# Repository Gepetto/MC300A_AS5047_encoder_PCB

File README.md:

# MC300_AS5047_encoder_PCB
This is a PCB support for a AS5047 magnetic encoder to replace MC300A control board on myactuator RMD-X actuators.

https://ams.com/en/as5047p
https://www.myactuator.com/_files/ugd/cab28a_d12405ad9d114c308658ca2bf5e42c5b.pdf

# Authors 
* Amine El Hamdaoui
* Jerome Manhes
* Thomas Flayols

LAAS CNRS

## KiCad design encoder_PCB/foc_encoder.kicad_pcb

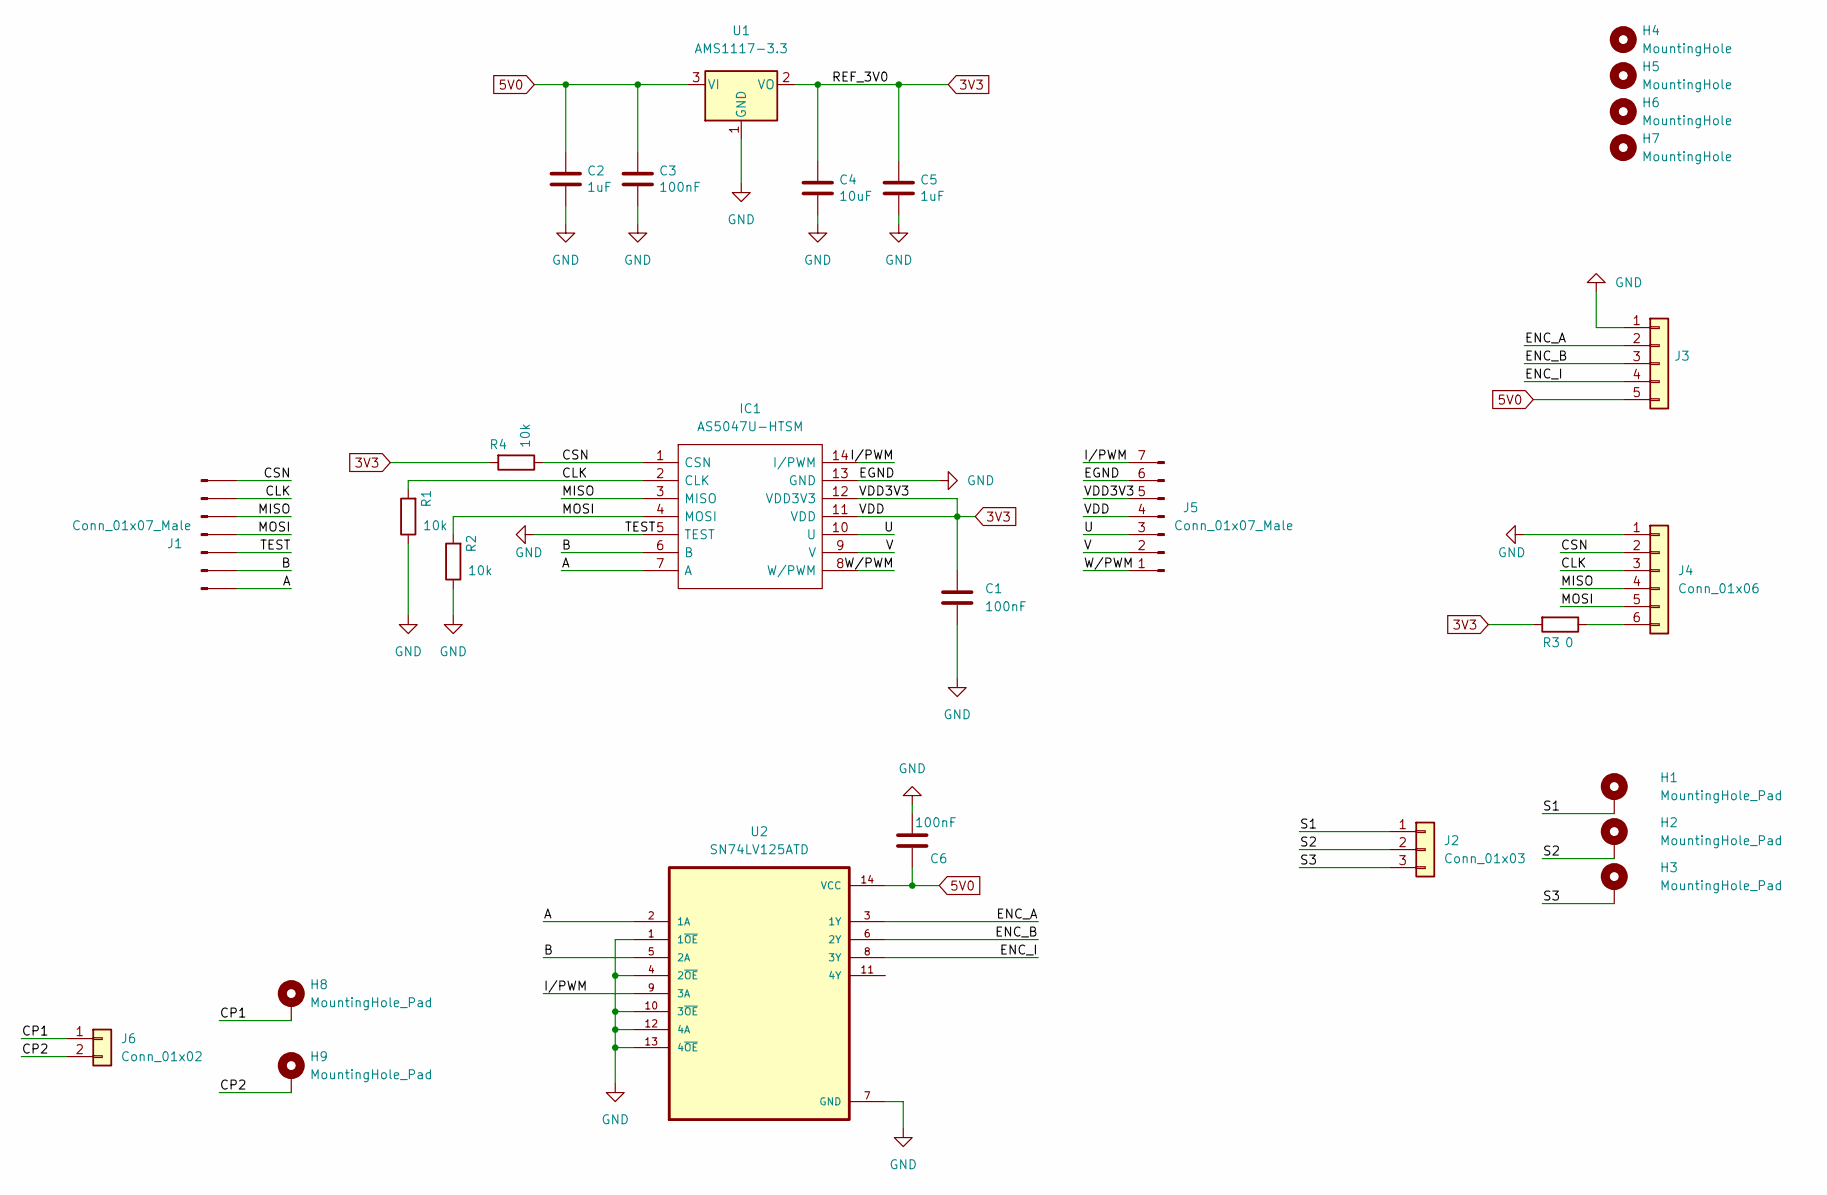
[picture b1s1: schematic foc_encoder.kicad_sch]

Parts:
C1, C6: 100nF; C_0402_1005Metric
C2, C5: 1uF; C_0402_1005Metric; Rated Voltage 10V; Part No GRM033C81A105ME05D; DigiKey 490-13219-1-ND
C3: 100nF; C_0402_1005Metric; Rated Voltage 10V; Part No GRM033R61E104KE14J; DigiKey 490-14571-1-ND
C4: 10uF; C_0402_1005Metric; Rated Voltage 10V; Part No GRM188R61A106ME69D; DigiKey 490-10475-1-ND
H1, H2, H3, H8, H9: MountingHole_Pad; MountingHole_2.2mm_M2_Pad
H4, H5, H6, H7: MountingHole; MountingHole_2.2mm_M2
IC1: AS5047U-HTSM; SOP65P640X110-14N; Manufacturer_Part_Number AS5047U-HTSM; Mouser Part Number 985-AS5047U-HTSM
J1, J5: Conn_01x07_Male; PinHeader_1x07_P2.54mm_Vertical
J2: Conn_01x03; AMASS_MR30PW-M_1x03_P3.50mm_Horizontal
J3: Hirose_DF13-05P-1.25DSA_1x05_P1.25mm_Vertical; Part No DF13-5P-1.25DSA; DigiKey H2194-ND
J4: Conn_01x06; Hirose_DF13-06P-1.25DSA_1x06_P1.25mm_Vertical
J6: Conn_01x02; Hirose_DF13-02P-1.25DSA_1x02_P1.25mm_Vertical
R1, R2, R4: 10k; R_0402_1005Metric
R3: 0; R_0402_1005Metric
U1: AMS1117-3.3; SOT-223-3_TabPin2
U2: SN74LV125ATD; SOIC127P600X175-14N

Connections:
3V3: C1.1, C4.1, C5.1, IC1.11 (VDD), IC1.12 (VDD3V3), J5.4, J5.5, R3.2, R4.2, U1.2 (VO)
5V0: C2.1, C3.1, C6.1, J3.5, U1.3 (VI), U2.14 (VCC)
/A: IC1.7 (A), J1.7, U2.2 (1A)
/B: IC1.6 (B), J1.6, U2.5 (2A)
/CLK: IC1.2 (CLK), J1.2, J4.3, R1.2
/CP1: H8.1, J6.1
/CP2: H9.1, J6.2
/CSN: IC1.1 (CSN), J1.1, J4.2, R4.1
/ENC_A: J3.2, U2.3 (1Y)
/ENC_B: J3.3, U2.6 (2Y)
/ENC_I: J3.4, U2.8 (3Y)
/I/PWM: IC1.14 (I/PWM), J5.7, U2.9 (3A)
/MISO: IC1.3 (MISO), J1.3, J4.4
/MOSI: IC1.4 (MOSI), J1.4, J4.5, R2.2
/S1: H1.1, J2.1
/S2: H2.1, J2.2
/S3: H3.1, J2.3
/U: IC1.10 (U), J5.3
/V: IC1.9 (V), J5.2
/W/PWM: IC1.8 (W/PWM), J5.1
GND: C1.2, C2.2, C3.2, C4.2, C5.2, C6.2, IC1.5 (TEST), IC1.13 (GND), J1.5, J3.1, J4.1, J5.6, R1.1, R2.1, U1.1 (GND), U2.1 (1~OE), U2.4 (2~OE), U2.7 (GND), U2.10 (3~OE), U2.12 (4A), U2.13 (4~OE)
unnamed: J4.6, R3.1

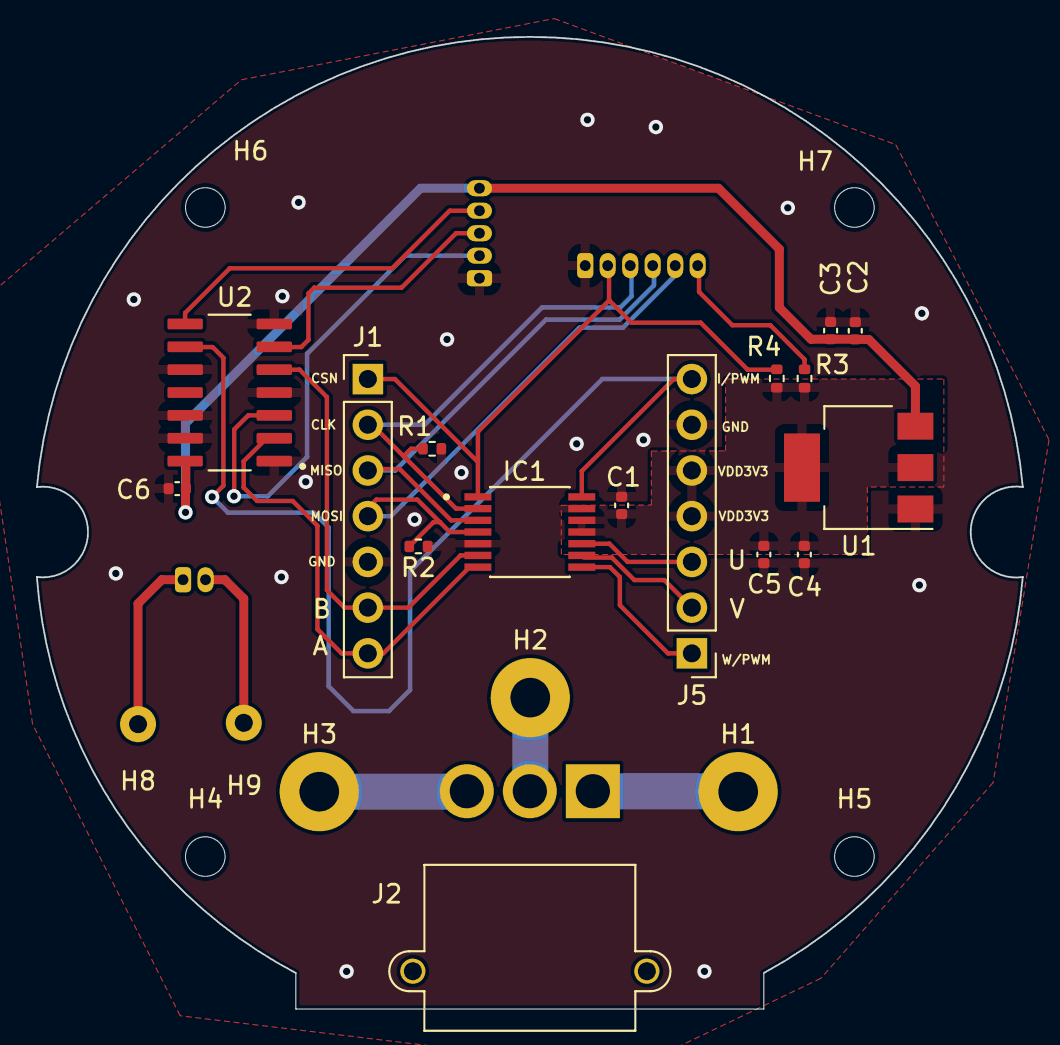
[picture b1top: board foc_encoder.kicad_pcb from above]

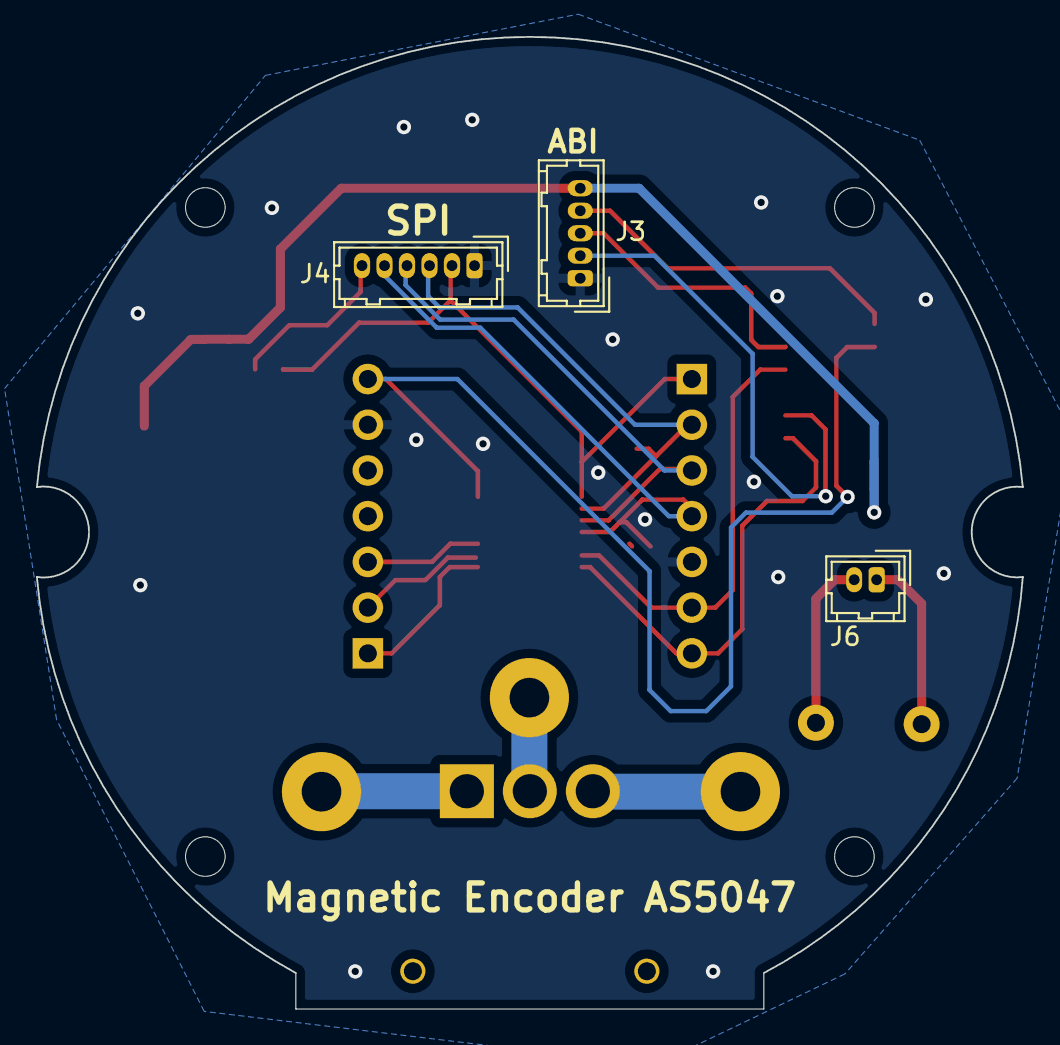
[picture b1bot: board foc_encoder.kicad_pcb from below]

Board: 2 copper layers, 54.8 x 54.0 mm, 28 parts (3 on the bottom side), 22 nets.
